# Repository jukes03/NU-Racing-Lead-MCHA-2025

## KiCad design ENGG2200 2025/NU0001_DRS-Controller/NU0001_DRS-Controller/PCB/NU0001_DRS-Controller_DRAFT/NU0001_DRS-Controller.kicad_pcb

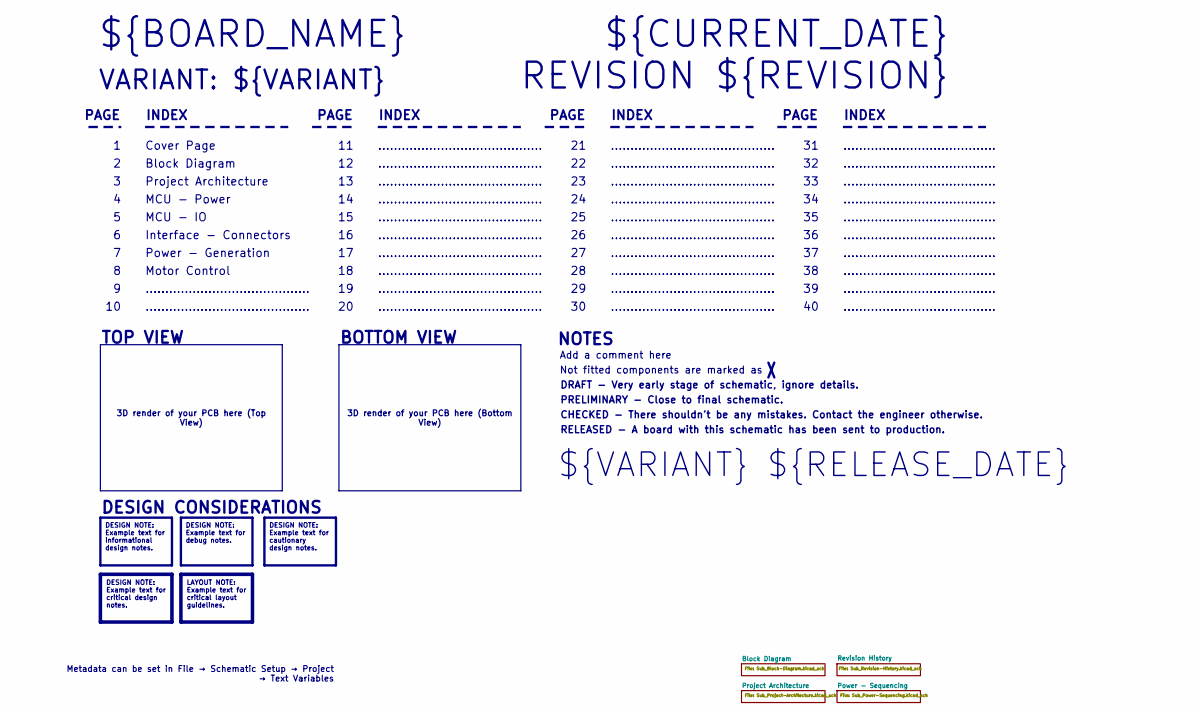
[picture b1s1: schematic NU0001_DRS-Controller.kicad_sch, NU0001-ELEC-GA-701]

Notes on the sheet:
BOTTOM VIEW
..........................................
RELEASED - A board with this schematic has been sent to production.
PAGE
TOP VIEW
Motor Control
Not fitted components are marked as
INDEX
PRELIMINARY - Close to final schematic.
${VARIANT} ${RELEASE_DATE}
MCU - Power
.......................................
${CURRENT_DATE}
VARIANT: ${VARIANT}
REVISION ${REVISION}
MCU - IO
${BOARD_NAME}
DRAFT - Very early stage of schematic, ignore details.
Interface - Connectors
Block Diagram
Add a comment here
Cover Page
NOTES
Project Architecture
CHECKED - There shouldn't be any mistakes. Contact the engineer otherwise.
DESIGN CONSIDERATIONS
Power - Generation
3D render of your PCB here (Bottom View)
3D render of your PCB here (Top View)
Metadata can be set in File → Schematic Setup → Project → Text Variables
DESIGN NOTE: Example text for informational design notes.
LAYOUT NOTE: Example text for critical layout guidelines.
DESIGN NOTE: Example text for cautionary design notes.
DESIGN NOTE: Example text for debug notes.
DESIGN NOTE: Example text for critical design notes.

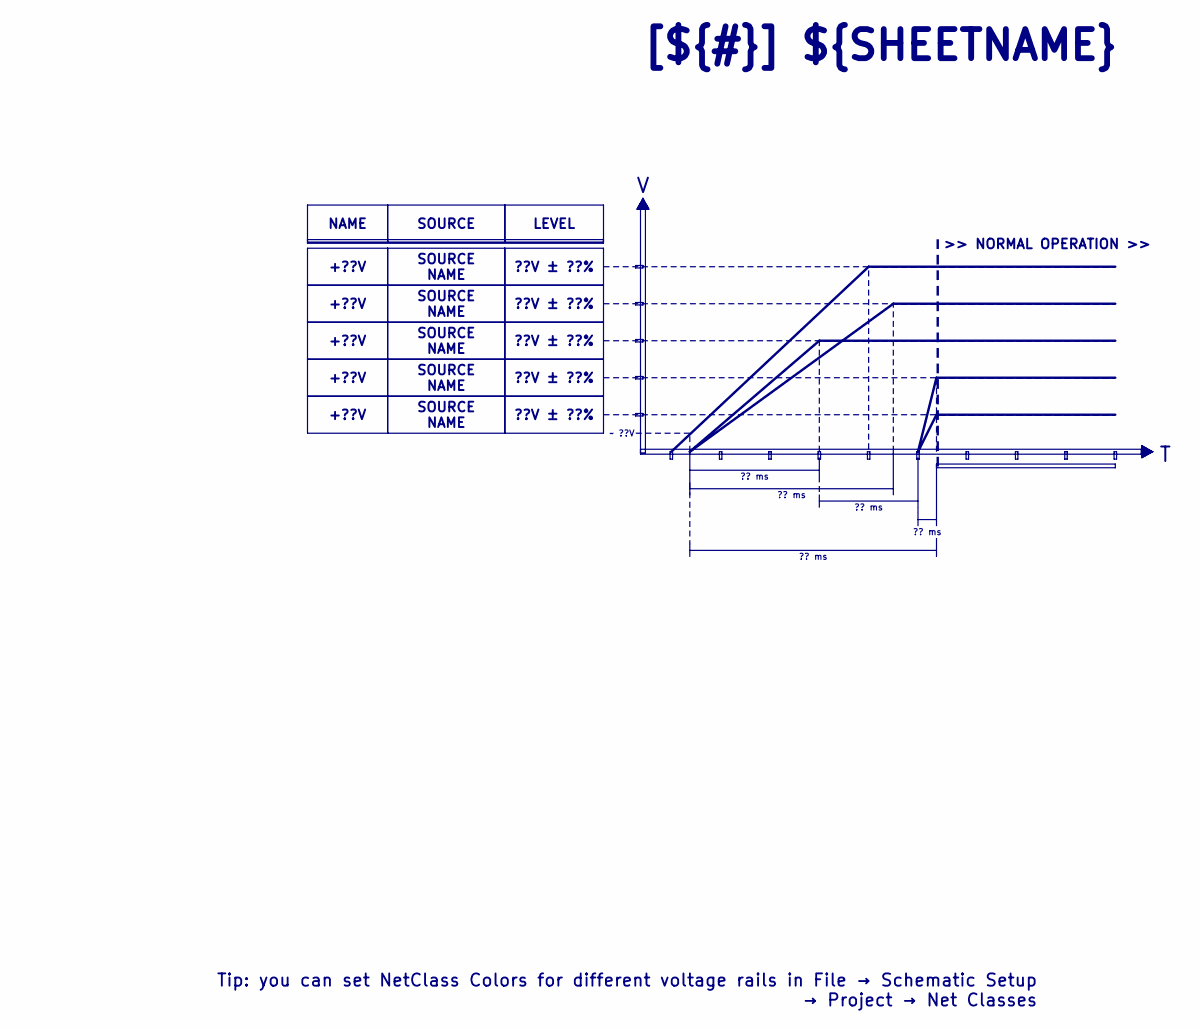
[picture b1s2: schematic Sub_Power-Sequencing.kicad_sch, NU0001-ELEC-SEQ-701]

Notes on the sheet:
>> NORMAL OPERATION >>
LEVEL
+??V
SOURCE NAME
?? ms
??V ± ??%
[${#}] ${SHEETNAME}
~ ??V
NAME
SOURCE
Tip: you can set NetClass Colors for different voltage rails in File → Schematic Setup → Project → Net Classes

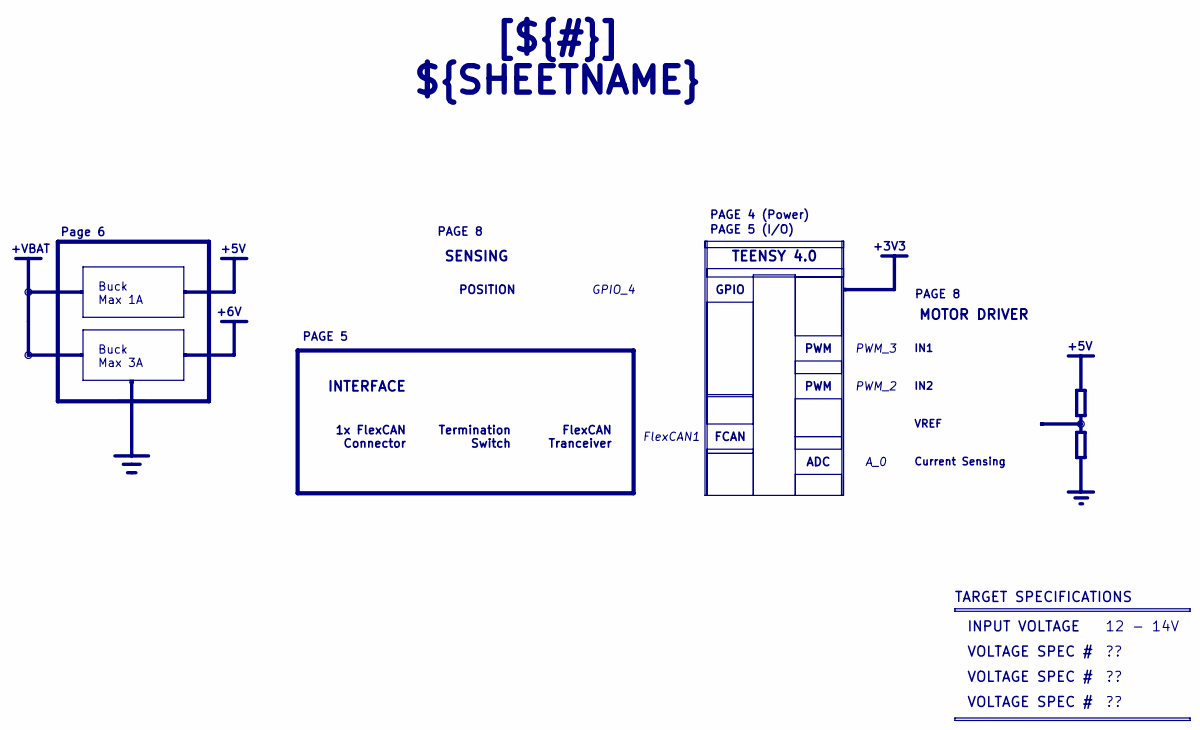
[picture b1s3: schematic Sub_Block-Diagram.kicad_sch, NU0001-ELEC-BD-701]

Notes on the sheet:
+5V
+6V
+3V3
+VBAT
VOLTAGE SPEC #
Buck Max 3A
TEENSY 4.0
PAGE 8
GPIO
PWM_3
INPUT VOLTAGE
GPIO_4
INTERFACE
MOTOR DRIVER
FlexCAN Tranceiver
POSITION
PAGE 5
VREF
Termination Switch
IN1
[${#}] ${SHEETNAME}
Page 6
TARGET SPECIFICATIONS
FCAN
SENSING
12 - 14V
ADC
PAGE 4 (Power)
1x FlexCAN Connector
PWM
PWM_2
Current Sensing
FlexCAN1
A_0
PAGE 5 (I/O)
Buck Max 1A
IN2

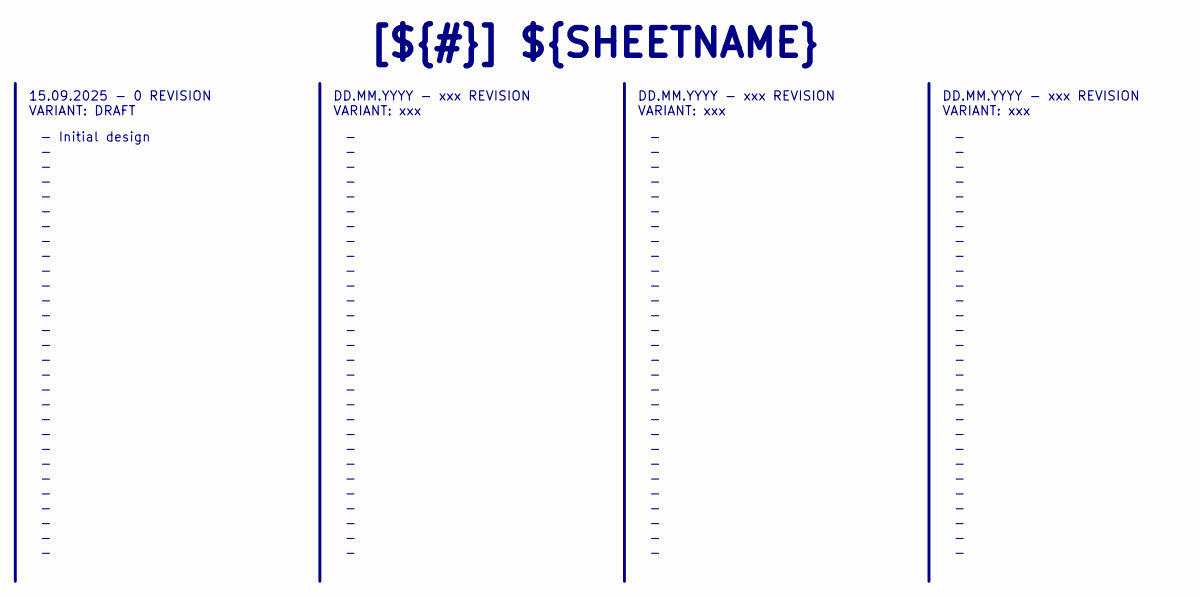
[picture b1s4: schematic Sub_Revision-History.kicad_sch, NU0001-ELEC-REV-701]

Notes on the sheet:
- - - - - - - - - - - - - - - - - - - - - - - - - - - - -
DD.MM.YYYY - xxx REVISION VARIANT: xxx
[${#}] ${SHEETNAME}
- Initial design - - - - - - - - - - - - - - - - - - - - - - - - - - - -
15.09.2025 - 0 REVISION VARIANT: DRAFT

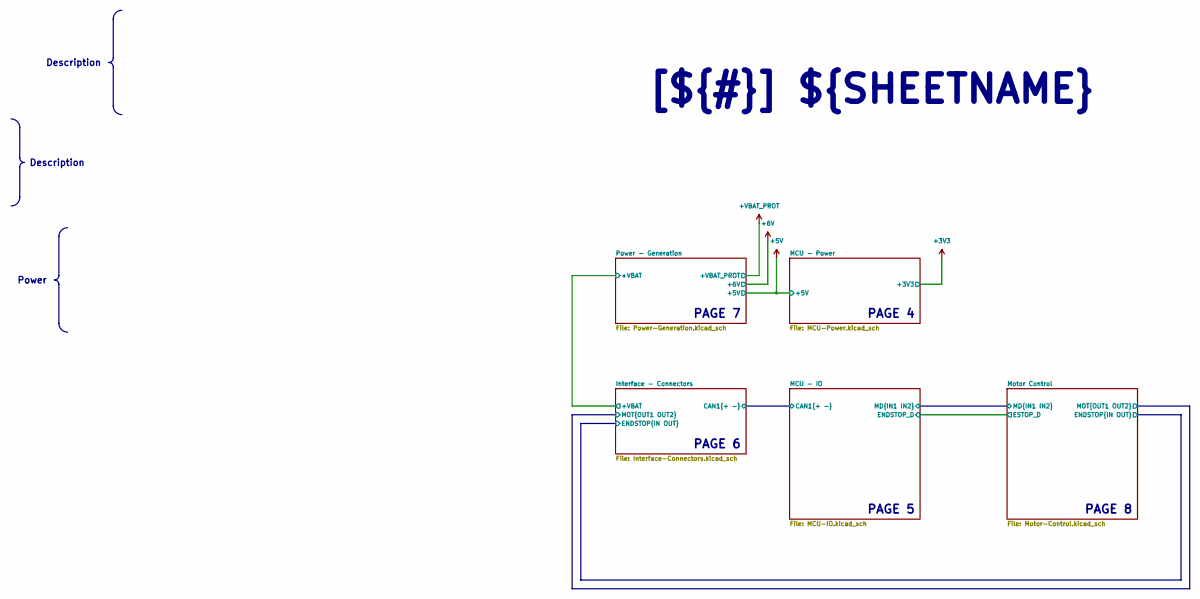
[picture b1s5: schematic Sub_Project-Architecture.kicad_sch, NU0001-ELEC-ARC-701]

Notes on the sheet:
PAGE 6
PAGE 4
PAGE 7
PAGE 5
PAGE 8
Description
[${#}] ${SHEETNAME}
Power

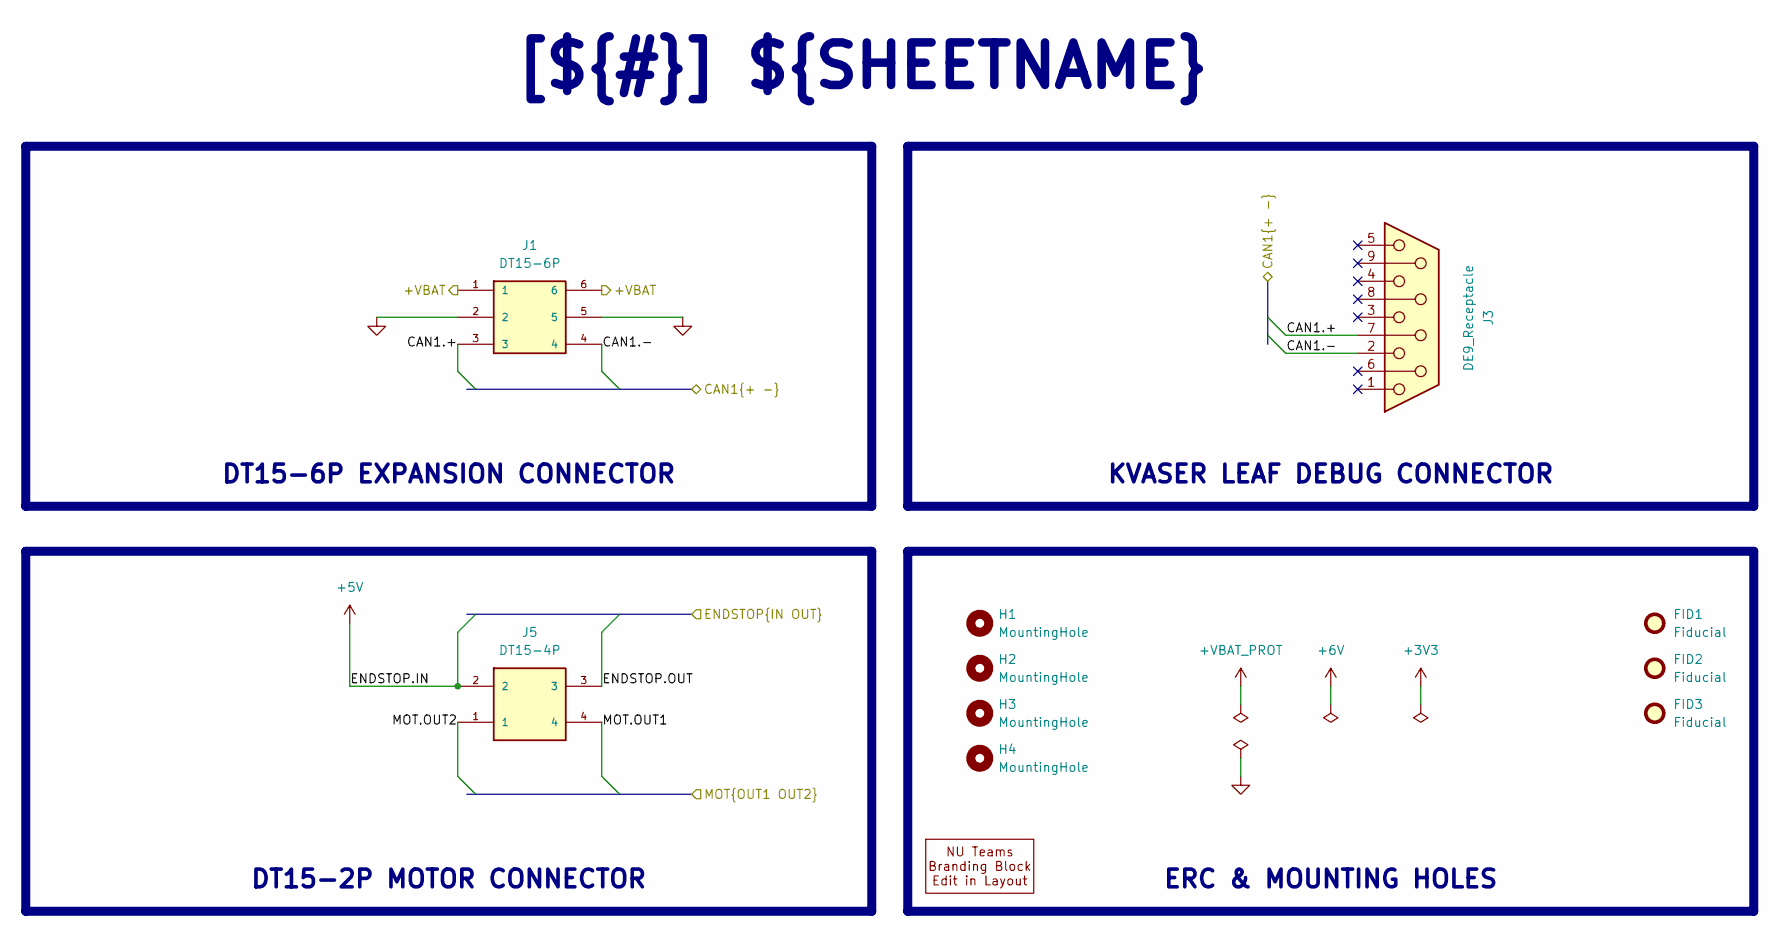
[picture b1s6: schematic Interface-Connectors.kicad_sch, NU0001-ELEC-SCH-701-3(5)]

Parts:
FID1, FID2, FID3: Fiducial; Fiducial_0.5mm_Mask1mm
H1, H2, H3, H4: MountingHole; MountingHole_3.2mm_M3_Pad_Via
J1: DT15-6P; PARTREV C1
J3: DE9_Receptacle; DSUB-9_Socket_Vertical_P2.77x2.84mm_MountingHoles
J5: DT15-4P; MPN DT15-4P
U3: Branding_Block_Teams; BRANDING_TEAMS

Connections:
+5V: J5.2; also elsewhere on the board
/Project Architecture/Interface - Connectors/+VBAT: J1.1, J1.6; also elsewhere on the board
/Project Architecture/Interface - Connectors/CAN1.+: J1.3, J3.7; also elsewhere on the board
/Project Architecture/Interface - Connectors/CAN1.-: J1.4, J3.2; also elsewhere on the board
/Project Architecture/Interface - Connectors/ENDSTOP.OUT: J5.3; also elsewhere on the board
/Project Architecture/Interface - Connectors/MOT.OUT1: J5.4; also elsewhere on the board
/Project Architecture/Interface - Connectors/MOT.OUT2: J5.1; also elsewhere on the board
GND: J1.2, J1.5; also elsewhere on the board

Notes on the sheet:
DT15-6P EXPANSION CONNECTOR
[${#}] ${SHEETNAME}
DT15-2P MOTOR CONNECTOR
KVASER LEAF DEBUG CONNECTOR
ERC & MOUNTING HOLES

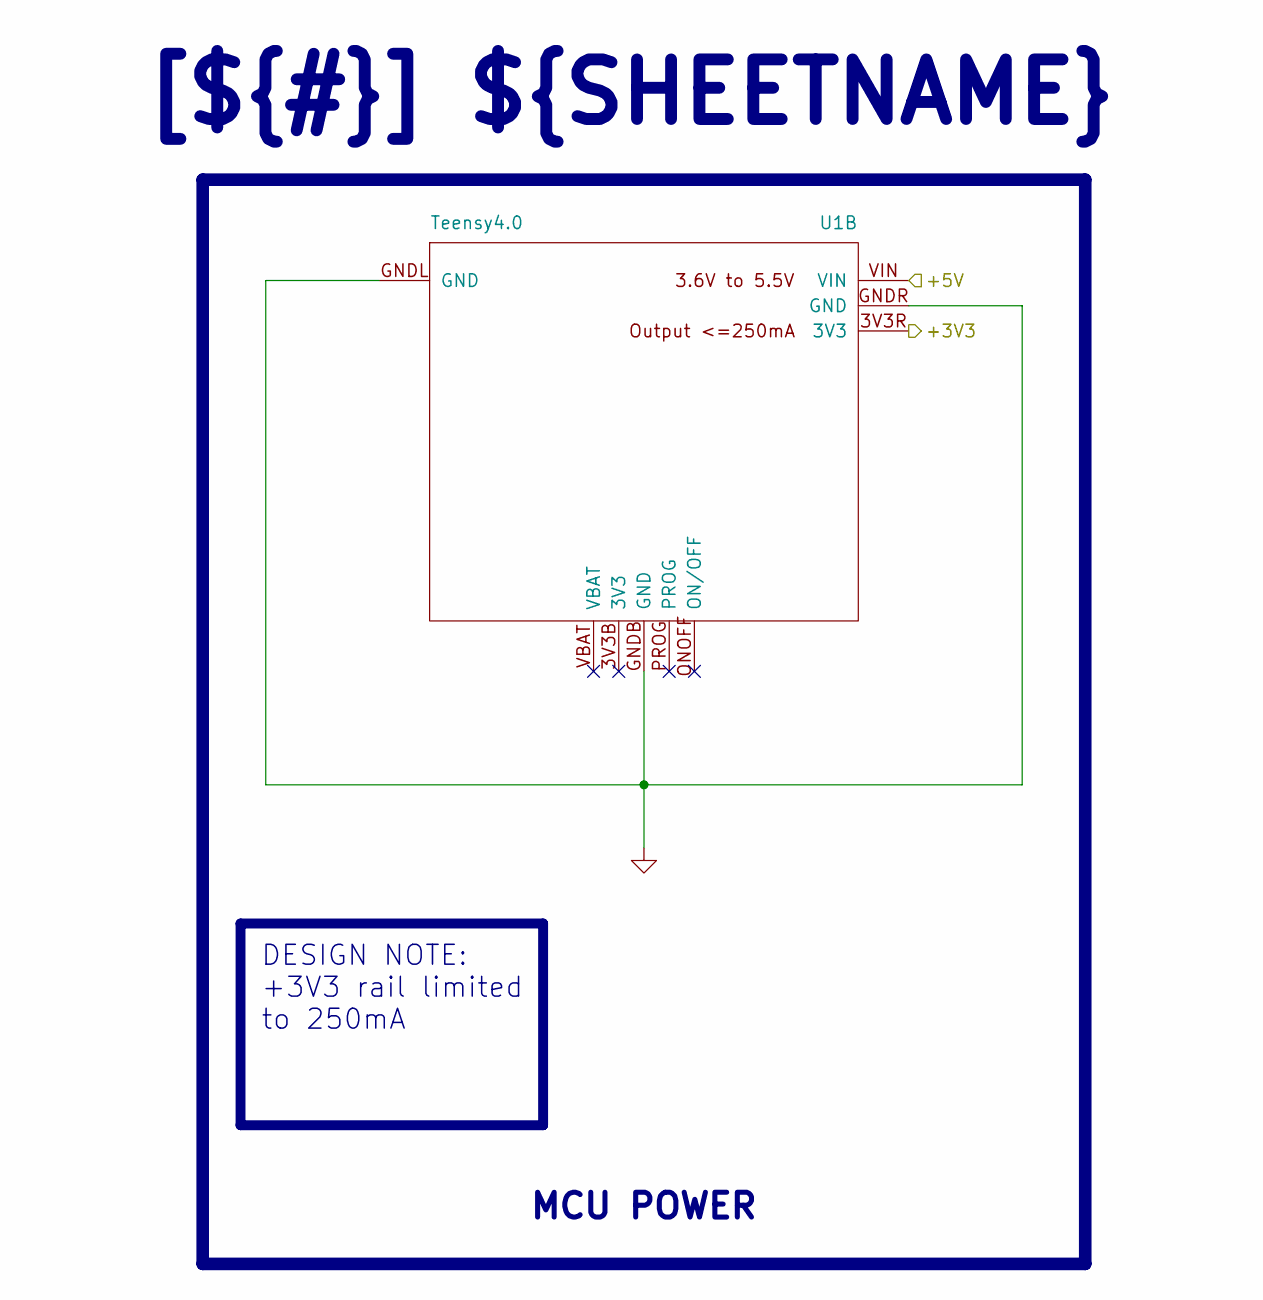
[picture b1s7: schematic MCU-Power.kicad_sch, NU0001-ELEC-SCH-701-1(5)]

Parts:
U1: Teensy4.0

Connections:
+3V3: U1.3V3R (3V3); also elsewhere on the board
+5V: U1.VIN; also elsewhere on the board
GND: U1.GNDB (GND), U1.GNDL (GND), U1.GNDR (GND); also elsewhere on the board

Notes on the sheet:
MCU POWER
DESIGN NOTE: +3V3 rail limited to 250mA
[${#}] ${SHEETNAME}

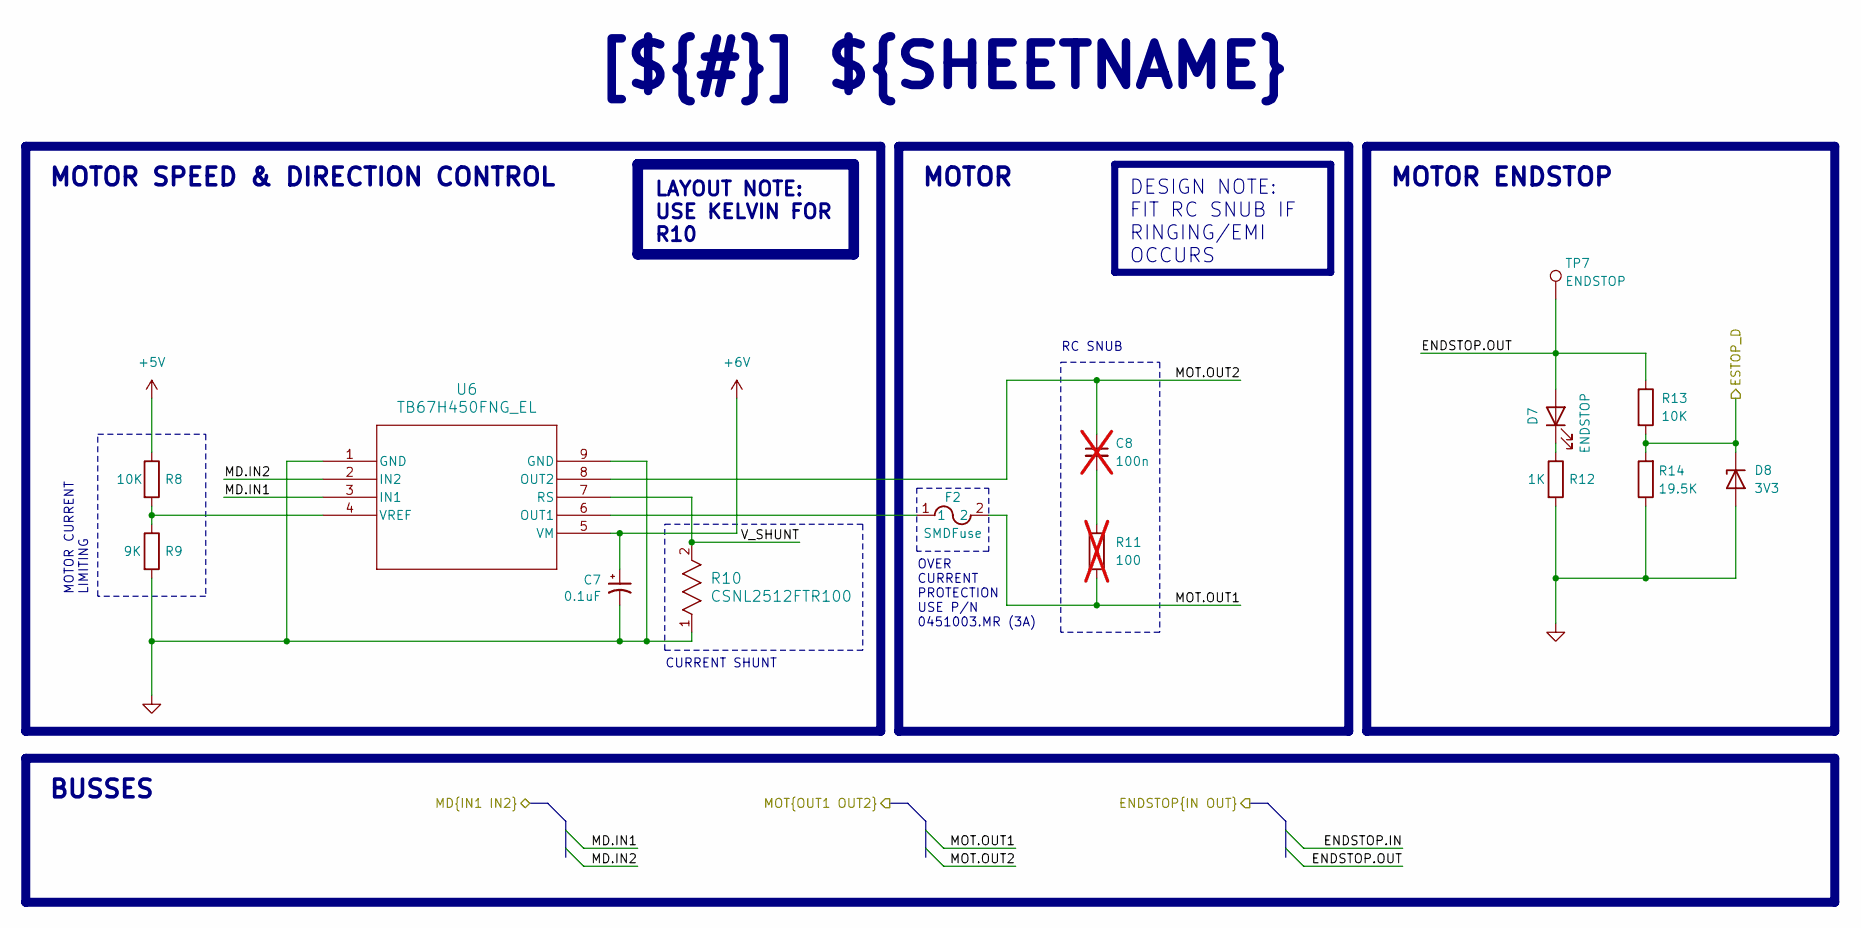
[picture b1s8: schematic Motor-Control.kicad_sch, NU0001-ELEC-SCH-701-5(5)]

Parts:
C7: 0.1uF; C_1206_3216Metric
C8: 100n; C_1206_3216Metric; not fitted
D7: ENDSTOP; LED_6UBC_XLG
D8: 3V3; D_SOD-123
F2: SMDFuse; FUSE_01550900M_LTF
R8, R13: 10K; R_1206_3216Metric
R9: 9K; R_1206_3216Metric
R10: CSNL2512FTR100; RES_CSNL2512_2_STP
R11: 100; R_1206_3216Metric; not fitted
R12: 1K; R_1206_3216Metric
R14: 19.5K; R_1206_3216Metric
TP7: ENDSTOP; TestPoint_Loop_D1.80mm_Drill1.0mm_Beaded
U6: TB67H450FNG_EL; P-HSOP8-0405-1p27-002_TOS

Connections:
+5V: R8.1; also elsewhere on the board
+6V: C7.1, U6.5 (VM); also elsewhere on the board
/Project Architecture/Interface - Connectors/ENDSTOP.OUT: D7.2 (A), R13.1, TP7.1; also elsewhere on the board
/Project Architecture/Interface - Connectors/MOT.OUT1: F2.2, R11.2; also elsewhere on the board
/Project Architecture/Interface - Connectors/MOT.OUT2: C8.1, U6.8 (OUT2); also elsewhere on the board
/Project Architecture/MCU - IO/ENDSTOP_D: D8.1 (K), R13.2, R14.2; also elsewhere on the board
/Project Architecture/MCU - IO/MD.IN1: U6.3 (IN1); also elsewhere on the board
/Project Architecture/MCU - IO/MD.IN2: U6.2 (IN2); also elsewhere on the board
/Project Architecture/Motor Control/V_SHUNT: R10.2, U6.7 (RS)
GND: C7.2, D8.2 (A), R9.2, R10.1, R12.2, R14.1, U6.1 (GND), U6.9 (GND); also elsewhere on the board
unnamed: C8.2, R11.1
unnamed: D7.1 (K), R12.1
unnamed: F2.1, U6.6 (OUT1)
unnamed: R8.2, R9.1, U6.4 (VREF)

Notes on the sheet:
MOTOR CURRENT LIMITING
RC SNUB
CURRENT SHUNT
OVER CURRENT PROTECTION USE P/N 0451003.MR (3A)
MOTOR ENDSTOP
MOTOR SPEED & DIRECTION CONTROL
MOTOR
DESIGN NOTE: FIT RC SNUB IF RINGING/EMI OCCURS
BUSSES
[${#}] ${SHEETNAME}
LAYOUT NOTE: USE KELVIN FOR R10

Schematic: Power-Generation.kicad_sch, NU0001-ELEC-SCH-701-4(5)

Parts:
C2: 120uF; PCAP_SVP_C6_PAN
C3: 1nF; C_1206_3216Metric
C4: 0.33uF; C_1206_3216Metric
C5: 470uF; CAP_EEFK_H13_PAN
C6: 0.1uF; C_1206_3216Metric
D1: +VBAT; LED_6UBC_XLG
D2, D4: SS34; D_SMA
D3: +VBAT_PROT; LED_6UBC_XLG
D5: +6V; LED_6UBC_XLG
D6: +5V; LED_6UBC_XLG
F1: SMDFuse; FUSE_01550900M_LTF
J4: COMMISIONING_PWR; TerminalBlock_Phoenix_MKDS-1,5-2_1x02_P5.00mm_Horizontal
L1: 33uH; IND_IHLP-6767DZ_VIS
R2, R3, R5: 1K; R_1206_3216Metric
R4: 3.9K; R_1206_3216Metric
R6, R7: 500; R_1206_3216Metric
TP3: +VBAT; TestPoint_Loop_D1.80mm_Drill1.0mm_Beaded
TP4: +VBAT_PROT; TestPoint_Loop_D1.80mm_Drill1.0mm_Beaded
TP5: +6V; TestPoint_Loop_D1.80mm_Drill1.0mm_Beaded
TP6: +5V; TestPoint_Loop_D1.80mm_Drill1.0mm_Beaded
U4: LM2596S-ADJ; TO-263-5_TabPin3
U5: LM7805_DPAK; TO-263-3_TabPin2

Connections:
+5V: C6.1, D6.2, TP6.1, U5.3 (VO); also elsewhere on the board
+6V: C3.1, C5.1, D5.2, L1.1, R4.1, TP5.1; also elsewhere on the board
+VBAT_PROT: C2.1, C4.1, D3.2, F1.2, TP4.1, U4.1 (VIN), U5.1 (VI)
/Project Architecture/Interface - Connectors/+VBAT: D1.2, D2.2 (A), J4.2, TP3.1; also elsewhere on the board
GND: C2.2, C4.2, C5.2, C6.2, D4.2 (A), J4.1, R2.2, R3.2, R5.2, R6.2, R7.2, U4.3 (GND), U4.5 (~ON/OFF), U5.2 (GND); also elsewhere on the board
unnamed: D1.1, R2.1
unnamed: D2.1 (K), F1.1
unnamed: D3.1, R3.1
unnamed: D4.1 (K), L1.2, U4.2 (OUT)
unnamed: D5.1, R6.1
unnamed: D6.1, R7.1
unnamed: C3.2, R4.2, R5.1, U4.4 (FB)

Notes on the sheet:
COMISSIONING INPUT
OVERCURRENT PROTECTION USE P/N 0451003.MR (3A)
REVERSE POLARITY PROTECTION
FEEDBACK
+5V GENERATION
[${#}] ${SHEETNAME}
PROTECTED INPUT
+6V GENERATION

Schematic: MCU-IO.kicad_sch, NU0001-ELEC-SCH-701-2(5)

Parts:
C1: 0.1uF; C_1206_3216Metric
R1: 120Ω; R_1206_3216Metric
SW1: DSIC01THGET; SW_DIP_SPSTx01_Slide_6.7x4.1mm_W7.62mm_P2.54mm_LowProfile
TP1: CAN_H1; TestPoint_Loop_D1.80mm_Drill1.0mm_Beaded
TP2: CAN_L1; TestPoint_Loop_D1.80mm_Drill1.0mm_Beaded
U1: Teensy4.0
U2: TJA1051T-3; SOIC-8_3.9x4.9mm_P1.27mm

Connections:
+3V3: U2.5 (VIO); also elsewhere on the board
+5V: C1.1, U2.3 (VCC); also elsewhere on the board
/Project Architecture/Interface - Connectors/CAN1.+: R1.1, TP1.1, U2.7 (CANH); also elsewhere on the board
/Project Architecture/Interface - Connectors/CAN1.-: SW1.2, TP2.1, U2.6 (CANL); also elsewhere on the board
/Project Architecture/MCU - IO/CTD.RX: U1.22 (22_CTX1~), U2.4 (RXD)
/Project Architecture/MCU - IO/CTD.TX: U1.23 (23_CRX1~), U2.1 (TXD)
/Project Architecture/MCU - IO/ENDSTOP_D: U1.4 (4_BCLK2~); also elsewhere on the board
/Project Architecture/MCU - IO/MD.IN1: U1.3 (3_LRCLK2~); also elsewhere on the board
/Project Architecture/MCU - IO/MD.IN2: U1.2 (2_OUT2~); also elsewhere on the board
GND: C1.2, U2.2 (GND), U2.8 (S); also elsewhere on the board
unnamed: R1.2, SW1.1

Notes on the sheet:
SWITCHABLE TERMINATION
CAN TRANCEIVER
MCU IO
[${#}] ${SHEETNAME}
BUSSES

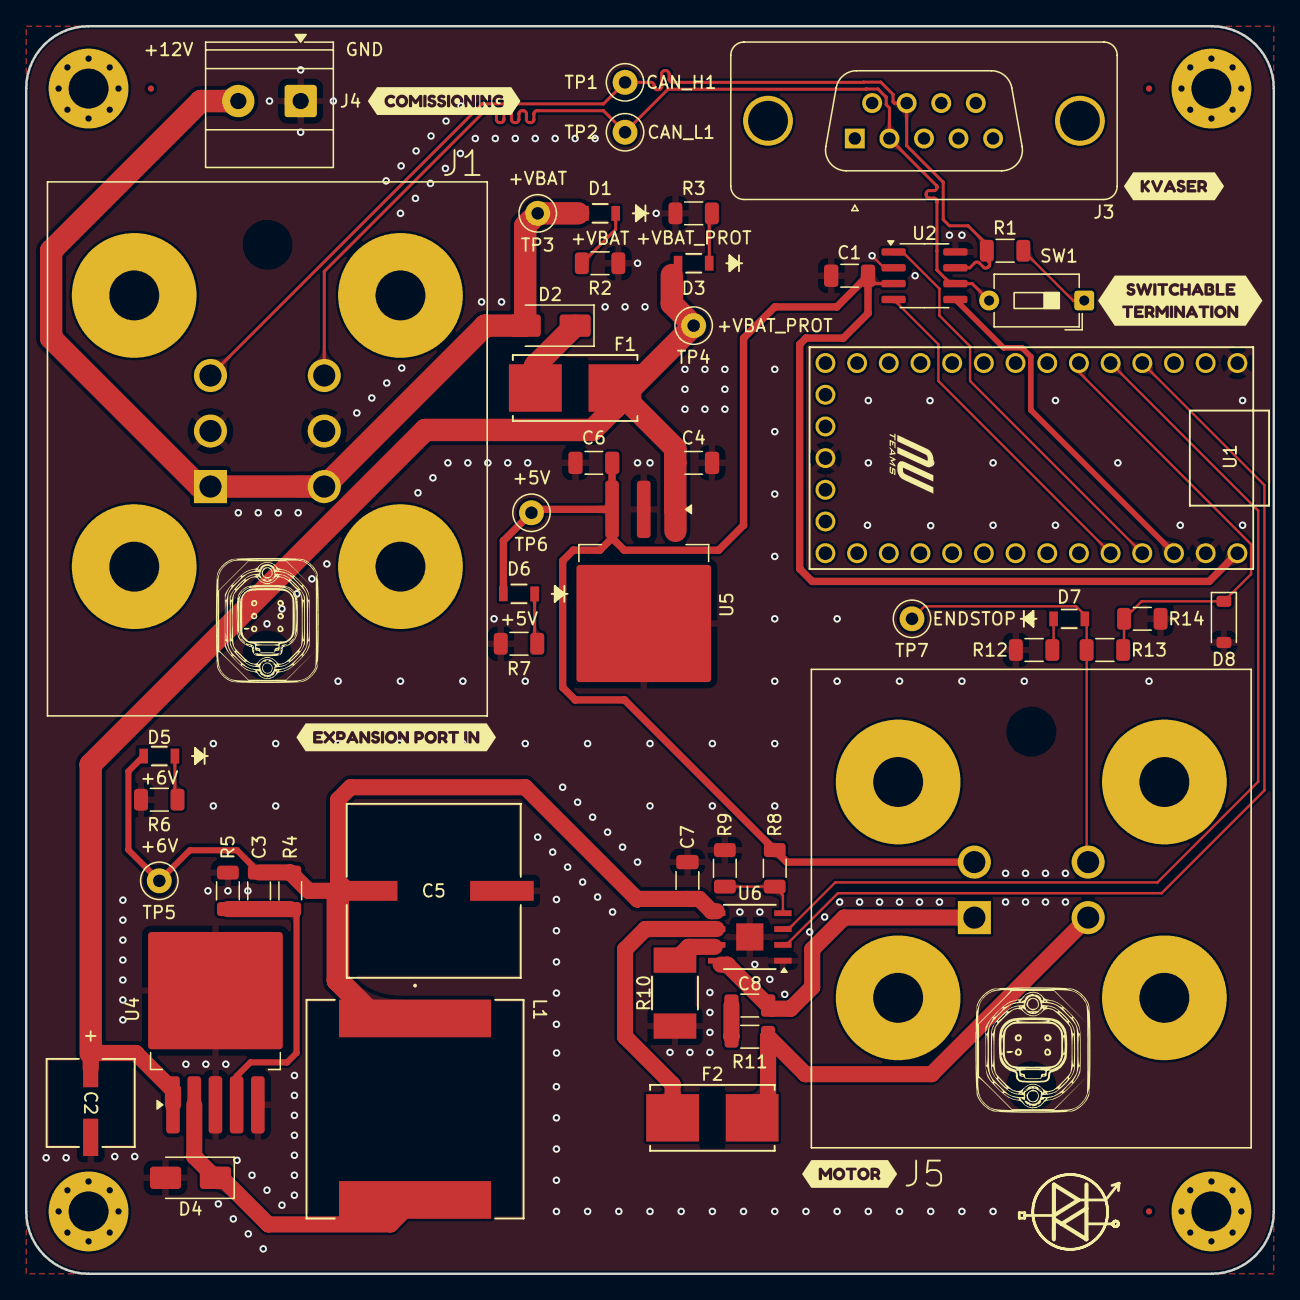
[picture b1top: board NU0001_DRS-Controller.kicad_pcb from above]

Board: 2 copper layers, 100.0 x 100.0 mm, 63 parts (0 on the bottom side), 29 nets.

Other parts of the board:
kibuzzard-68CA21AE: G***; kibuzzard-68CA21AE
kibuzzard-68CA21C7: G***; kibuzzard-68CA21C7
kibuzzard-68CA21E3: G***; kibuzzard-68CA21E3
kibuzzard-68CA22D8: G***; kibuzzard-68CA22D8
kibuzzard-68CA1631: G***; kibuzzard-68CA1631

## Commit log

2025-01-04 correction
2025-01-08 mcha team structure
2025-01-15 lvd connector
2025-01-17 alec's lead mcha report
2025-01-20 report, rules, mcha structure
2025-01-22 broken HVD (MSD) connector???
2025-01-27 prep for budget list, AT connectors
2025-01-27 thangs, issues repo
2025-01-28 budget, hv connectors, wheel speed sensors
2025-01-28 diary entry for 27-01-25
2025-01-29 budget, AT connectors, 18 pin on CEN>HIP loom
2025-01-30 at connectors, moving notes to onenote, budget
2025-01-30 lena's report
2025-01-30 notes on iteration to av.one
2025-02-03 at connectors and new HVD (MSD) interlock connector
2025-02-03 budget, at/dt connectors
2025-02-04 collating notes from diarly app
2025-02-04 nu25 dbc added to things to implement
2025-02-05 tasks, ota, task overview, AVone budget
    changed all todo list things into an excel so i can track their progressions and due dates
2025-02-05 hv connectors, expansion board scope change
2025-02-06 moving SWEN functionality to expansion board
2025-02-07 hv connectors
    step files and figuring out cost
2025-02-10 tasks, rules enquiry decision between red on CEN or HIP and couple things with project set out
2025-02-10 same as last
2025-02-11 hour tracker, week 0 presso prep
2025-02-11 lvd interpose to cen
2025-02-11 esp32 wireless code upload, hip to dcdc connector
2025-02-11 ota with esp32-c6
2025-02-12 brake temp sensors, reports
2025-02-12 bits
2025-02-13 nu26 accum cell selection
2025-02-13 NU25 Connector Pinout for entire car
2025-02-14 hv connectors, nu25 connector pinout schematic
    ordered the hv connectors into files for where they will go
    continued work on the nu25 schematic
2025-02-16 accum stuff for connector pin out
    thinking of calling this file "NU25_MCHA_Systems"
2025-02-16 accum wiring mostly done
    need to add in fan banks (simplified version)
2025-02-16 same as last commit
2025-02-16 haywards report and bms/imd fault detection circuit in-depth
2025-02-16 wheel speed sensor datasheet
2025-02-16 couple small changes
    hv wires are orange now
2025-02-17 scopes scopes scopes, week 0 preso
2025-02-18 nu25 electrical overview
    motor controller pin out
    estops
    shutdown circuit breaks
2025-02-18 remaining of nu25 connector pinout to nu25 electrical system overview
2025-02-19 reports, no mchas, preso and goals and critical dates
2025-02-20 0 fyp scopes document
2025-02-21 gantt chart making
2025-02-21 gantt chart
2025-02-24 jackson report, gantt chart
2025-02-25 gantt chart, nucan zero to hero, alec 4200 report
2025-02-25 goals and objectives for the year
2025-02-26 gantt chart
    adjusting timeline for bspd and pen, as those are the two systems that jayson will be working on
2025-02-27 mcha projects, gantt chart
2025-02-28 made rules folder, clarification document on TSSI, NUCAN ZtoH
2025-03-08 gantt chart removal of HFR_TSSI
2025-03-13 big push
2025-03-18 havent done push in a while
    - starter project deliverables
    - engg3200 scope file on obsidian
2025-03-19 file reorganise
2025-03-19 bushy lead mcha report, scope doc
2025-03-31 bms stuff, energy meter, scopes, packing list
2025-04-01 mcha bible data sheets
2025-04-01 update file name of mcha tech inspection datasheets
2025-04-01 hv connectors
2025-04-02 3200 scopes
2025-04-15 gantt chart update
    - added alec's gantt chart to the folder
2025-04-29 push
    havent done push in a while
2025-05-09 push
    - track days, connectors, gantt chart
2025-05-23 file update
    - havent done push for a while
    - 3200 scope stuff
    - hv connectors
2025-05-26 hv connectors, gantt chart
    - got all the part numbers for the extra components i (hopefully) need for the HIP to DCDC & HIP to EM connectors
    - updated gantt chart to suit for more lv system tests
    - added 2024 to 2025 rule change document
2025-05-26 I_CEN data over a range of track days
2025-05-31 reports, gantt chart updates
2025-06-03 invoices, datasheets, packing list
2025-06-04 budget update
2025-06-04 hip to mc connector update
2025-06-04 file moving of HV connectors
2025-06-06 datahsets
2025-06-30 can tests, packing list, reports, dyno progress meeting, mosfets, 'how to' documents
2025-07-02 budget, teensys, washers, stuff stuff
2025-07-03 reports, teensy heartbeat code, connector pinouts
2025-07-07 comp stuff
2025-07-15 reports, hv connectors, ESF stuff, datasheets, budget
2025-07-18 asana, comp, esf
2025-07-24 reports, asana, 4200
2025-07-30 budget, asana, dyno test, 4200 scope document
2025-08-04 scope, asana
2025-08-10 4200 scope doc, canking output, track packing list, datasheets
2025-08-21 budget stuffs, hv connectors, datasheets, motec ztoh, flow rate, packing list, 4200 scope form
2025-08-26 datasheets, tech, cells, asana
2025-09-08 knowledge transfer, asana
2025-09-12 asana and tech
2025-09-25 asana, LVR, 2200, datasheets
2026-01-02 big push of shit idk what this is
2026-01-02 expansion board testing idk
2026-01-07 final push???
    idk what this is
2026-01-08 Create Part B Performance Template.xlsx
    template
2026-01-08 performance review
2026-01-11 reports
2026-01-11 thangs from main pc
2026-01-11 FIANL: FIANL FINAL: FINAL
    report tshit
